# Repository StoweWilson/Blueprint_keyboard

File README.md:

## What my project is 
My project is a 64% keyboard designed to resemble the layout of an Apple Magic Keyboard, with a few keys rearranged on either side of the PCB. There will be two magnetic pogo pins on either side, which will allow the keypad with identical pogo pins to connect, as well as allowing the keypad to be placed on either side of the keyboard, therefore making it modular. The case takes inspiration from the Worklouder XYZ Work Board.

## Why I made the project
I really like low-profile 60%–65% keyboards but had trouble finding ones that fit my needs. Learning that I had to put my own spin on the idea, I decided to take on the challenge of adding a keypad while keeping it modular, so I could still have the compactness of a 64% keyboard with the ability to have a numpad that does not make it bulky.

## Images

### Keyboard

### Keypad

### Render

## BOM
### Keyboard

|Product name|Product Description|Qty|Price|Product Link|
|------------|-------------------|---|-----|------------|
|ATmega32U4-A|AVR AVR® ATmega Microcontroller IC 8-Bit 16MHz 32KB (16K x 16) FLASH 44-TQFP (10x10)|1|5.29|https://www.digikey.com/en/products/detail/microchip-technology/ATMEGA32U4-AU/1914602|
|16 MHz Crystal|CRYSTAL 3225 16MHZ 20PF 10PPM|1|.18|https://www.digikey.com/en/products/detail/eaton-electronics-division/E3X160201Y08/25656418?gclsrc=aw.ds&gad_source=1&gad_campaignid=20509818236&gbraid=0AAAAADrbLlgS94xmC2OHtv7KUQTO5uOa0&gclid=Cj0KCQiAx8PKBhD1ARIsAKsmGbeNFFstWFqMior3PH_CgvAHFOVgZvViWWTwkzizrjl1ohLOkbDwLqwaAlaHEALw_wcB|
|USB6B1 ESD Protector|TVS DIODE 5.25VWM 8SOIC|1|.69|https://www.digikey.com/en/products/detail/stmicroelectronics/USB6B1RL/654663|https://www.digikey.com/en/products/detail/amphenol-icc-fci-/10171746-00021LF/24366718?gclsrc=aw.ds&gad_source=1&gad_campaignid=20504594076&gbraid=0AAAAADrbLliKa-isyfEEG1K0mhQ-IdK9f&gclid=Cj0KCQiAx8PKBhD1ARIsAKsmGbfS4QL507NDol1-6Cdh5rUTj5M5hC5s0NrW_j3S6W67Z4K-qavOG4UaAp8YEALw_wcB|
|USB-C Receptacle (USB 2.0)|USB C RECEPTACLE R/A SMT 16P G/F|1|.72|https://www.digikey.com/en/products/detail/amphenol-icc-fci-/10171746-00021LF/24366718?gclsrc=aw.ds&gad_source=1&gad_campaignid=20504594076&gbraid=0AAAAADrbLliKa-isyfEEG1K0mhQ-IdK9f&gclid=Cj0KCQiAx8PKBhD1ARIsAKsmGbfS4QL507NDol1-6Cdh5rUTj5M5hC5s0NrW_j3S6W67Z4K-qavOG4UaAp8YEALw_wcB|
|10 kΩ|RES 10 OHM 1% 1/8W 0805|2|.11|https://www.digikey.com/en/products/detail/yageo/RC0805FR-1310RL/13694343?gclsrc=aw.ds&gad_source=1&gad_campaignid=17335707486&gbraid=0AAAAADrbLlj7rEgZ30rWPo_IyYLBKIC1T&gclid=Cj0KCQiAx8PKBhD1ARIsAKsmGbe2BlRAZ_fbKZ1YBvA79CHduwhXdcr3Sd3RQTWvr3wtoWWFxpEhsnEaAhrXEALw_wcB|
|22 Ω|RES 22 OHM 1% 1/8W 0805|2|.11|https://www.digikey.com/en/products/detail/yageo/RC0805FR-1322RL/13694339?gclsrc=aw.ds&gad_source=1&gad_campaignid=17335707486&gbraid=0AAAAADrbLlj7rEgZ30rWPo_IyYLBKIC1T&gclid=Cj0KCQiAx8PKBhD1ARIsAKsmGbfZP3-md_kWXjVo2urg73f88iKE2tR9Xip3xlEVRXTp1bbZVnmvqCgaAlWkEALw_wcB|
|5.1 kΩ|RES 5.1K OHM 5% 1/8W 0805|2|.10|https://www.digikey.com/en/products/detail/yageo/RC0805JR-075K1L/728338|
|22 pF|22 pF ±5% 50V Ceramic Capacitor C0G, NP0 0603 (1608 Metric)|2|.12|https://www.digikey.com/en/products/detail/kemet/C0603C220J5GACTU/411055|
|1 µF|CAP CER 1UF 6.3V X5R 0402|1|.08|https://www.digikey.com/en/products/detail/samsung-electro-mechanics/CL05A104KA5NNNC/3886701|
|.1uF|0.1 µF ±10% 25V Ceramic Capacitor X5R 0402 (1005 Metric)|4|.08|https://www.digikey.com/en/products/detail/samsung-electro-mechanics/CL05A104KA5NNNC/3886701|
|Diode|DIODE STANDARD 100V 150MA SOD123|64|.11|https://www.digikey.com/en/products/detail/diodes-incorporated/1N4148W-7-F/814371|
|Reset Button|SWITCH TACTILE SPST-NO 0.05A 12V|1|.41|https://www.digikey.ca/en/products/detail/c-k/Y97KT23B2NAFP/9649861|
|Adafruit 5413 Magnetic Connector|four 0.1" spaced contact pogo pins and a right angl|4|2.13|https://www.aliexpress.us/p/shoppingcart/index.html?spm=a2g0o.detail.0.0.2397nvtbnvtbTw|

### Keypad
|Product name|Product Description|Qty|Price|Product Link|
|------------|-------------------|---|-----|------------|
|XIAO RP2040 SMD|XIAO RP2040 SMD|1|4.68|https://www.digikey.com/en/products/detail/seeed-technology-co-ltd/102010428/14672129?gclsrc=aw.ds&gad_source=1&gad_campaignid=20243136172&gbraid=0AAAAADrbLlj-cx_AB7IYmSUrHfcZ3IQLC&gclid=Cj0KCQiAx8PKBhD1ARIsAKsmGbcn_ZEg4zv6ObEisLv_b6IgijRfvJiZc21Bz6JM8BaIT7ggCM4oFr8aAoSUEALw_wcB|
|PCF8575DBR I/O Expander|IC XPNDR 400KHZ I2C SMBUS 24SSOP|1|3.58|https://www.digikey.com/en/products/detail/texas-instruments/PCF8575DBR/754551|
|10 kΩ|RES 10 OHM 1% 1/8W 0805|4|.11|https://www.digikey.com/en/products/detail/yageo/RC0805FR-1310RL/13694343?gclsrc=aw.ds&gad_source=1&gad_campaignid=17335707486&gbraid=0AAAAADrbLlj7rEgZ30rWPo_IyYLBKIC1T&gclid=Cj0KCQiAx8PKBhD1ARIsAKsmGbe2BlRAZ_fbKZ1YBvA79CHduwhXdcr3Sd3RQTWvr3wtoWWFxpEhsnEaAhrXEALw_wcB|
|5.1 kΩ|RES 5.1K OHM 5% 1/8W 0805|2|.10|https://www.digikey.com/en/products/detail/yageo/RC0805JR-075K1L/728338|
|Diode|DIODE STANDARD 100V 150MA SOD123|21|.11|https://www.digikey.com/en/products/detail/diodes-incorporated/1N4148W-7-F/814371|
|Adafruit 5413 Magnetic Connector|four 0.1" spaced contact pogo pins and a right angl|4|2.13|https://www.aliexpress.us/p/shoppingcart/index.html?spm=a2g0o.detail.0.0.2397nvtbnvtbTw|

### Notes
- Shipping is not included in any of the prices.
- PCB with shippiing is $59.04 Qty of 5 each can't change.
- I will pay for the keyboard switches with my own money.

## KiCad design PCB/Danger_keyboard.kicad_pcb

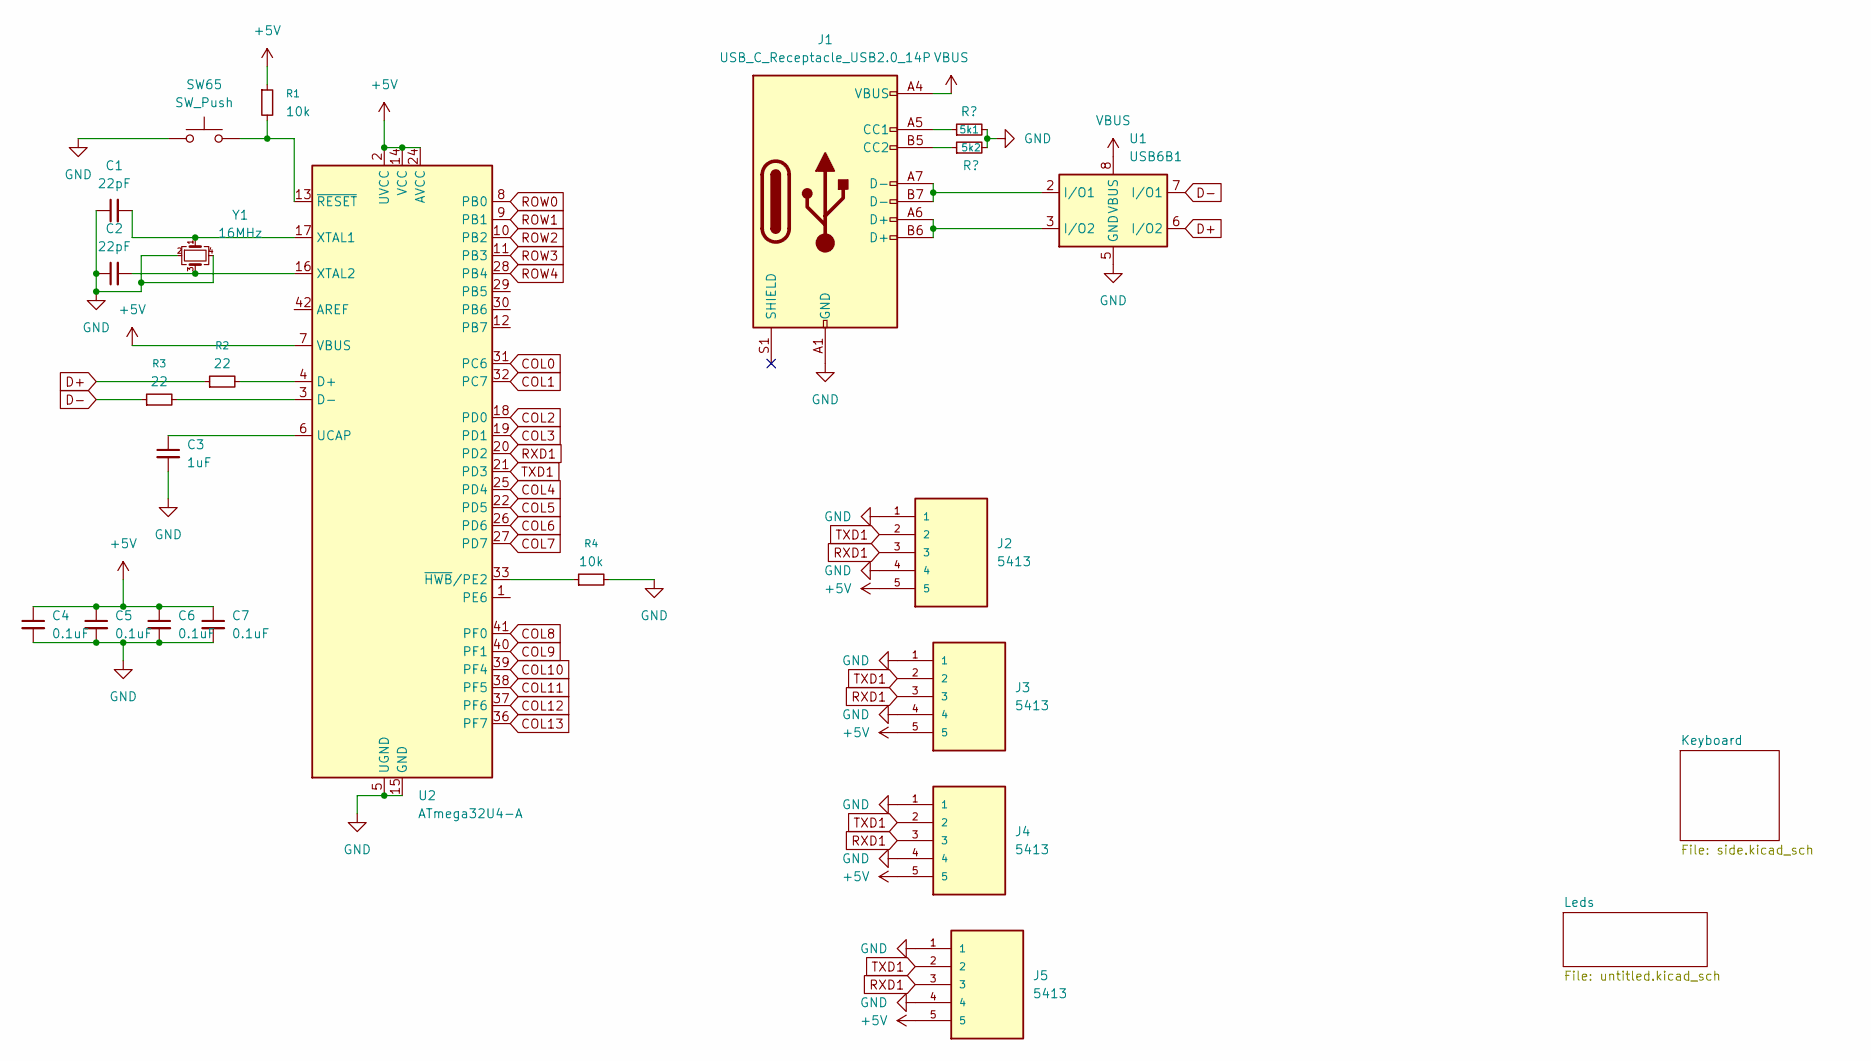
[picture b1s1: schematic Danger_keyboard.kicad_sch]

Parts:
5k1, 5k2: R?; R_0805_2012Metric
C1, C2: 22pF; C_0805_2012Metric
C3: 1uF; C_0805_2012Metric
C4, C5, C6, C7: 0.1uF; C_0805_2012Metric
J1: USB_C_Receptacle_USB2.0_14P; USB_C_Receptacle_GCT_USB4105-xx-A_16P_TopMnt_Horizontal
J2, J3, J4, J5: 5413; ADAFRUIT_5413; PARTREV X1
R1, R4: 10k; R_0805_2012Metric
R2, R3: 22; R_0805_2012Metric
SW65: SW_Push; SW_SPST_PTS647_Sx38
U1: USB6B1; SOIC-8_3.9x4.9mm_P1.27mm
U2: ATmega32U4-A; TQFP-44_10x10mm_P0.8mm
Y1: 16MHz; Crystal_SMD_3225-4Pin_3.2x2.5mm

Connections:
+5V: C4.1, C5.1, C6.1, C7.1, J2.5, J3.5, J4.5, J5.5, R1.1, U2.2 (UVCC), U2.7 (VBUS), U2.14 (VCC), U2.24 (AVCC), U2.34 (VCC), U2.44 (AVCC)
COL0: U2.31 (PC6); also elsewhere on the board
COL1: U2.32 (PC7); also elsewhere on the board
COL2: U2.18 (PD0); also elsewhere on the board
COL3: U2.19 (PD1); also elsewhere on the board
COL4: U2.25 (PD4); also elsewhere on the board
COL5: U2.22 (PD5); also elsewhere on the board
COL6: U2.26 (PD6); also elsewhere on the board
COL7: U2.27 (PD7); also elsewhere on the board
COL8: U2.41 (PF0); also elsewhere on the board
COL9: U2.40 (PF1); also elsewhere on the board
COL10: U2.39 (PF4); also elsewhere on the board
COL11: U2.38 (PF5); also elsewhere on the board
COL12: U2.37 (PF6); also elsewhere on the board
COL13: U2.36 (PF7); also elsewhere on the board
D+: R2.1, U1.6 (I/O2)
D-: R3.1, U1.7 (I/O1)
GND: 5k1.2, 5k2.2, C1.1, C2.1, C3.2, C4.2, C5.2, C6.2, C7.2, J1.A1 (GND), J1.A12 (GND), J1.B1 (GND), J1.B12 (GND), J2.1, J2.4, J3.1, J3.4, J4.1, J4.4, J5.1, J5.4, R4.2, SW65.1, U1.4 (GND), U1.5 (GND), U2.5 (UGND), U2.15 (GND), U2.23 (GND), U2.35 (GND), U2.43 (GND), Y1.2, Y1.4
unnamed: 5k1.1, J1.A5 (CC1)
unnamed: 5k2.1, J1.B5 (CC2)
unnamed: J1.A6 (D+), J1.B6 (D+), U1.3 (I/O2)
unnamed: J1.A7 (D-), J1.B7 (D-), U1.2 (I/O1)
unnamed: R2.2, U2.4 (D+)
unnamed: R3.2, U2.3 (D-)
unnamed: C3.1, U2.6 (UCAP)
unnamed: C1.2, U2.17 (XTAL1), Y1.1
unnamed: C2.2, U2.16 (XTAL2), Y1.3
unnamed: R4.1, U2.33 (~HWB/PE2)
unnamed: R1.2, SW65.2, U2.13 (~RESET)
ROW0: U2.8 (PB0); also elsewhere on the board
ROW1: U2.9 (PB1); also elsewhere on the board
ROW2: U2.10 (PB2); also elsewhere on the board
ROW3: U2.11 (PB3); also elsewhere on the board
ROW4: U2.28 (PB4); also elsewhere on the board
RXD1: J2.3, J3.3, J4.3, J5.3, U2.20 (PD2)
TXD1: J2.2, J3.2, J4.2, J5.2, U2.21 (PD3)
VBUS: J1.A4 (VBUS), J1.A9 (VBUS), J1.B4 (VBUS), J1.B9 (VBUS), U1.1 (VBUS), U1.8 (VBUS)

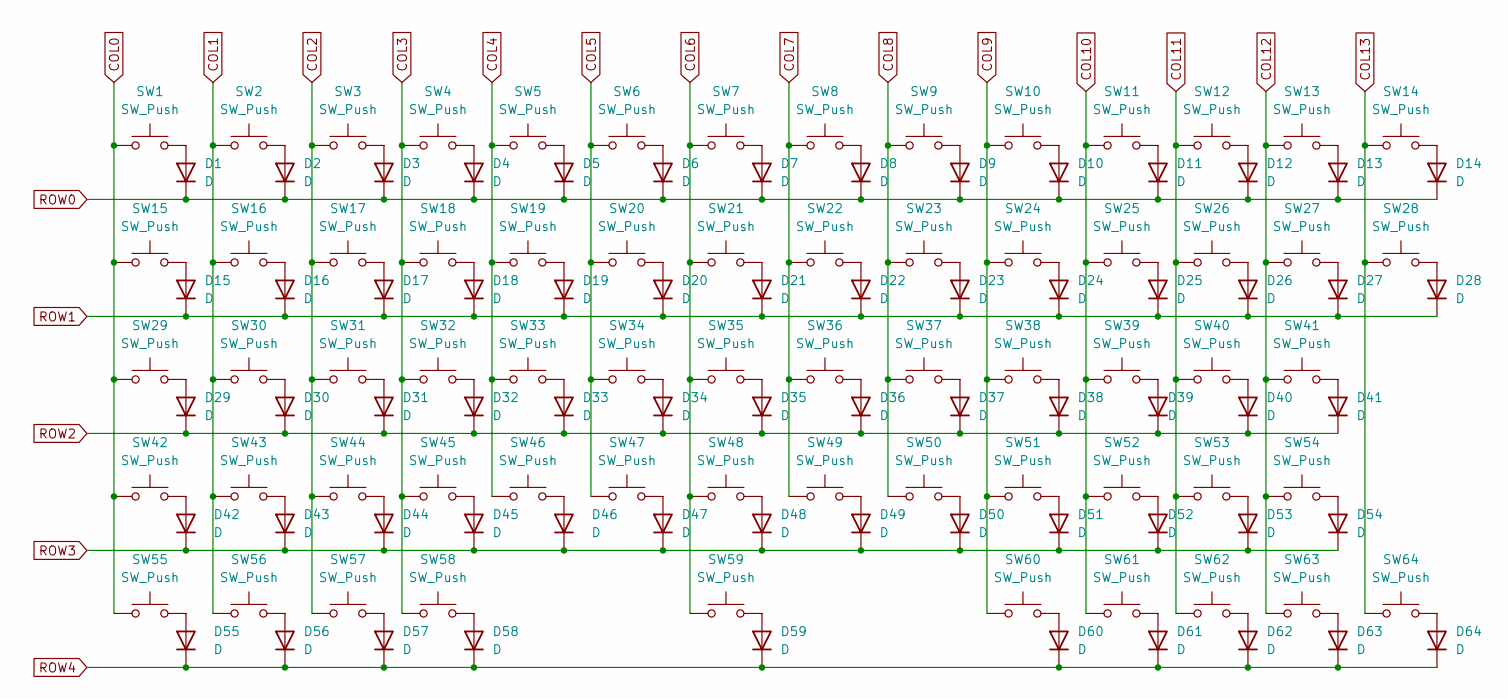
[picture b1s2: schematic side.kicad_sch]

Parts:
D1, D2, D3, D4, D5, D6, D7, D8, D9, D10, D11, D12, D13, D14, D15, D16, D17, D18, D19, D20, D21, D22, D23, D24, D25, D26, D27, D28, D29, D30, D31, D32, D33, D34, D35, D36, D37, D38, D39, D40, D41, D42, D43, D44, D45, D46, D47, D48, D49, D50, D51, D52, D53, D54, D55, D56, D57, D58, D59, D60, D61, D62, D63, D64: D; D_SOD-123
SW1, SW2, SW3, SW4, SW5, SW6, SW7, SW8, SW9, SW10, SW11, SW12, SW13, SW14, SW15, SW16, SW17, SW18, SW19, SW20, SW21, SW22, SW23, SW24, SW25, SW26, SW27, SW28, SW29, SW30, SW31, SW32, SW33, SW34, SW35, SW36, SW37, SW38, SW39, SW40, SW41, SW42, SW43, SW44, SW45, SW46, SW47, SW48, SW49, SW50, SW51, SW52, SW53, SW54, SW55, SW56, SW57, SW58, SW59, SW60, SW61, SW62, SW63, SW64: SW_Push; SW_Gateron_LowProfile_HotSwap_PTH

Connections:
COL0: SW1.1, SW15.1, SW29.1, SW42.1, SW55.1; also elsewhere on the board
COL1: SW2.1, SW16.1, SW30.1, SW43.1, SW56.1; also elsewhere on the board
COL2: SW3.1, SW17.1, SW31.1, SW44.1, SW57.1; also elsewhere on the board
COL3: SW4.1, SW18.1, SW32.1, SW45.1, SW58.1; also elsewhere on the board
COL4: SW5.1, SW19.1, SW33.1, SW46.1; also elsewhere on the board
COL5: SW6.1, SW20.1, SW34.1, SW47.1; also elsewhere on the board
COL6: SW7.1, SW21.1, SW35.1, SW48.1, SW59.1; also elsewhere on the board
COL7: SW8.1, SW22.1, SW36.1, SW49.1; also elsewhere on the board
COL8: SW9.1, SW23.1, SW37.1, SW50.1; also elsewhere on the board
COL9: SW10.1, SW24.1, SW38.1, SW51.1, SW60.1; also elsewhere on the board
COL10: SW11.1, SW25.1, SW39.1, SW52.1, SW61.1; also elsewhere on the board
COL11: SW12.1, SW26.1, SW40.1, SW53.1, SW62.1; also elsewhere on the board
COL12: SW13.1, SW27.1, SW41.1, SW54.1, SW63.1; also elsewhere on the board
COL13: SW14.1, SW28.1, SW64.1; also elsewhere on the board
unnamed: D1.2 (A), SW1.2
unnamed: D2.2 (A), SW2.2
unnamed: D3.2 (A), SW3.2
unnamed: D4.2 (A), SW4.2
unnamed: D5.2 (A), SW5.2
unnamed: D6.2 (A), SW6.2
unnamed: D7.2 (A), SW7.2
unnamed: D8.2 (A), SW8.2
unnamed: D9.2 (A), SW9.2
unnamed: D10.2 (A), SW10.2
unnamed: D11.2 (A), SW11.2
unnamed: D12.2 (A), SW12.2
unnamed: D13.2 (A), SW13.2
unnamed: D14.2 (A), SW14.2
unnamed: D15.2 (A), SW15.2
unnamed: D16.2 (A), SW16.2
unnamed: D17.2 (A), SW17.2
unnamed: D18.2 (A), SW18.2
unnamed: D19.2 (A), SW19.2
unnamed: D20.2 (A), SW20.2
unnamed: D21.2 (A), SW21.2
unnamed: D22.2 (A), SW22.2
unnamed: D23.2 (A), SW23.2
unnamed: D24.2 (A), SW24.2
unnamed: D25.2 (A), SW25.2
unnamed: D26.2 (A), SW26.2
unnamed: D27.2 (A), SW27.2
unnamed: D28.2 (A), SW28.2
unnamed: D29.2 (A), SW29.2
unnamed: D30.2 (A), SW30.2
unnamed: D31.2 (A), SW31.2
unnamed: D32.2 (A), SW32.2
unnamed: D33.2 (A), SW33.2
unnamed: D34.2 (A), SW34.2
unnamed: D35.2 (A), SW35.2
unnamed: D36.2 (A), SW36.2
unnamed: D37.2 (A), SW37.2
unnamed: D38.2 (A), SW38.2
unnamed: D39.2 (A), SW39.2
unnamed: D40.2 (A), SW40.2
unnamed: D41.2 (A), SW41.2
unnamed: D42.2 (A), SW42.2
unnamed: D43.2 (A), SW43.2
unnamed: D44.2 (A), SW44.2
unnamed: D45.2 (A), SW45.2
unnamed: D46.2 (A), SW46.2
unnamed: D47.2 (A), SW47.2
unnamed: D48.2 (A), SW48.2
unnamed: D49.2 (A), SW49.2
unnamed: D50.2 (A), SW50.2
unnamed: D51.2 (A), SW51.2
unnamed: D52.2 (A), SW52.2
unnamed: D53.2 (A), SW53.2
unnamed: D54.2 (A), SW54.2
unnamed: D55.2 (A), SW55.2
unnamed: D56.2 (A), SW56.2
unnamed: D57.2 (A), SW57.2
unnamed: D58.2 (A), SW58.2
unnamed: D59.2 (A), SW59.2
unnamed: D60.2 (A), SW60.2
unnamed: D61.2 (A), SW61.2
unnamed: D62.2 (A), SW62.2
unnamed: D63.2 (A), SW63.2
unnamed: D64.2 (A), SW64.2
ROW0: D1.1 (K), D2.1 (K), D3.1 (K), D4.1 (K), D5.1 (K), D6.1 (K), D7.1 (K), D8.1 (K), D9.1 (K), D10.1 (K), D11.1 (K), D12.1 (K), D13.1 (K), D14.1 (K); also elsewhere on the board
ROW1: D15.1 (K), D16.1 (K), D17.1 (K), D18.1 (K), D19.1 (K), D20.1 (K), D21.1 (K), D22.1 (K), D23.1 (K), D24.1 (K), D25.1 (K), D26.1 (K), D27.1 (K), D28.1 (K); also elsewhere on the board
ROW2: D29.1 (K), D30.1 (K), D31.1 (K), D32.1 (K), D33.1 (K), D34.1 (K), D35.1 (K), D36.1 (K), D37.1 (K), D38.1 (K), D39.1 (K), D40.1 (K), D41.1 (K); also elsewhere on the board
ROW3: D42.1 (K), D43.1 (K), D44.1 (K), D45.1 (K), D46.1 (K), D47.1 (K), D48.1 (K), D49.1 (K), D50.1 (K), D51.1 (K), D52.1 (K), D53.1 (K), D54.1 (K); also elsewhere on the board
ROW4: D55.1 (K), D56.1 (K), D57.1 (K), D58.1 (K), D59.1 (K), D60.1 (K), D61.1 (K), D62.1 (K), D63.1 (K), D64.1 (K); also elsewhere on the board

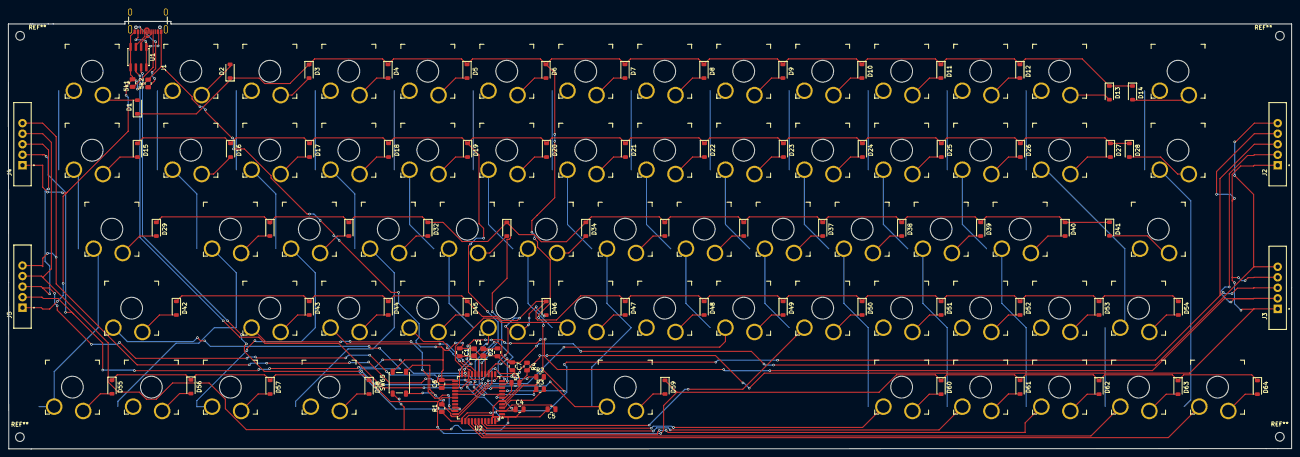
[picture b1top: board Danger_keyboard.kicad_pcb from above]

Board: 2 copper layers, 309.5 x 103.1 mm, 150 parts (0 on the bottom side), 101 nets.

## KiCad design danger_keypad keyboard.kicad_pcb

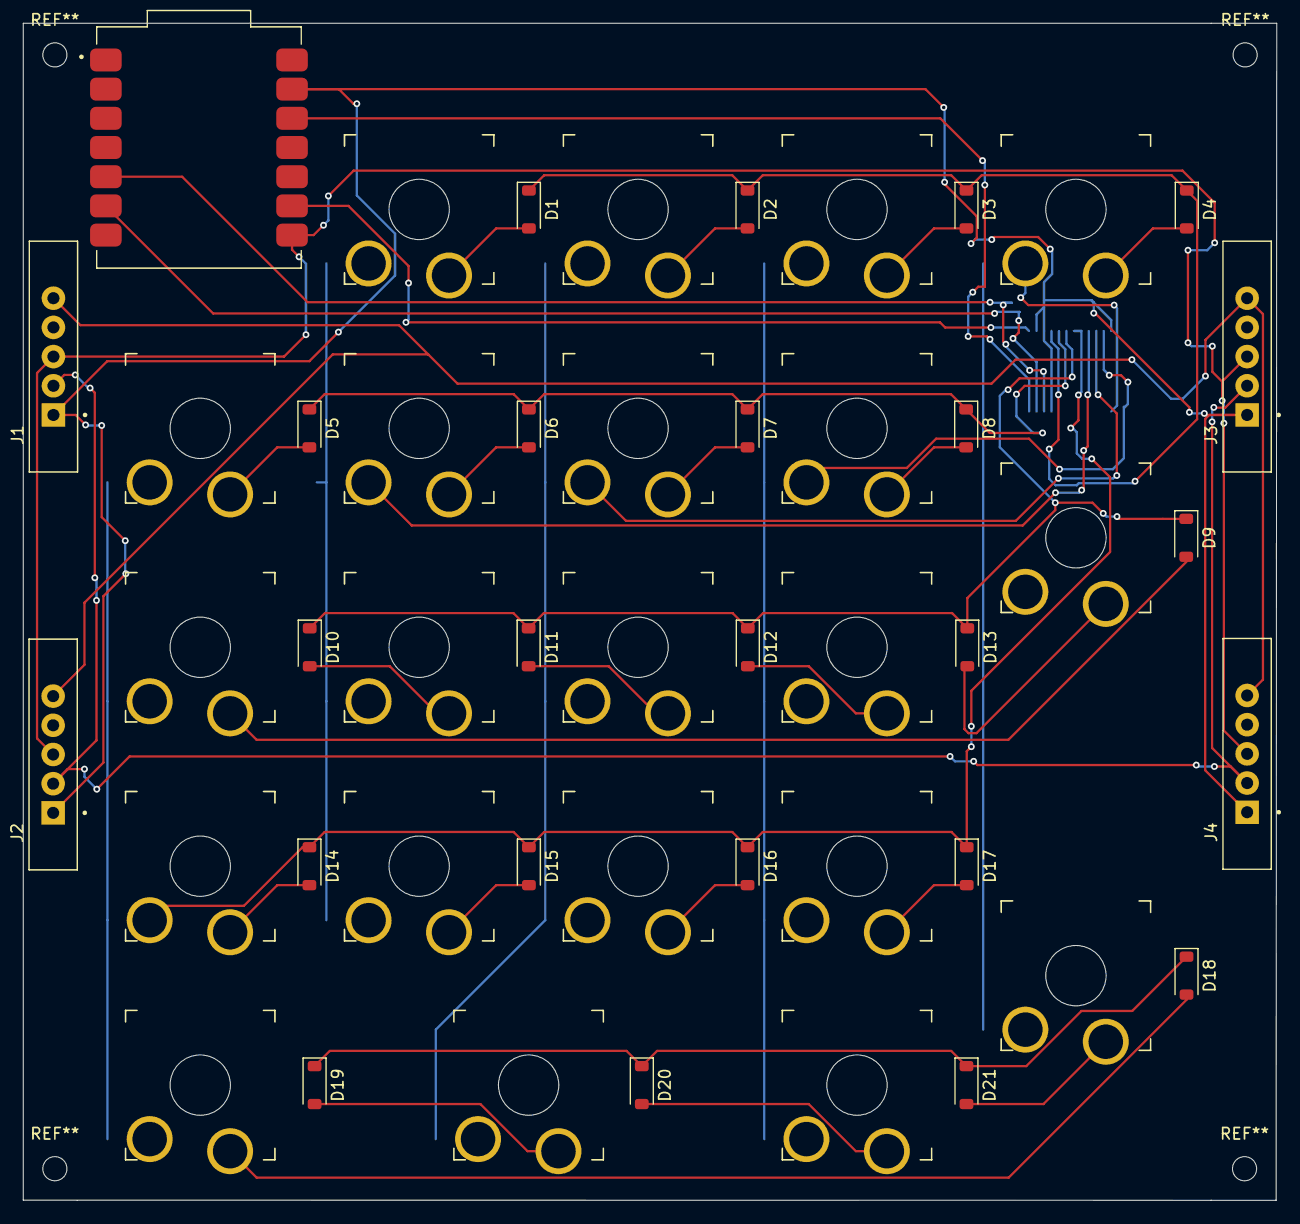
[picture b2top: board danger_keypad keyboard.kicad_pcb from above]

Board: 2 copper layers, 109.1 x 102.4 mm, 48 parts (1 on the bottom side), 38 nets.

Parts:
D1, D2, D3, D4, D5, D6, D7, D8, D9, D10, D11, D12, D13, D14, D15, D16, D17, D18, D19, D20, D21: D; D_SOD-123
J1, J2, J3, J4: 5413; ADAFRUIT_5413
SW1, SW2, SW3, SW4, SW5, SW6, SW7, SW8, SW9, SW10, SW11, SW12, SW13, SW14, SW15, SW16, SW17, SW18, SW19, SW20, SW21: SW_Push; SW_Gateron_LowProfile_HotSwap_PTH
U1: XIAO-RP2040-SMD; MODULE_102010428
U2: PCF8575DBR; SSOP-24_5.3x8.2mm_P0.65mm

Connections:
3V: U1.12 (3V3), U2.24 (VCC)
+5V: J1.5, J2.5, J3.5, J4.5
GND: J1.1, J2.1, J3.1, J4.1, U1.13 (GND), U2.2 (A1), U2.3 (A2), U2.12 (GND), U2.21 (A0)
Key_Col1: D14.1 (K), D15.1 (K), D16.1 (K), D17.1 (K), SW5.1, SW10.1, SW14.1, SW19.1, U2.7 (P3), U2.8 (P4)
Key_Col2: SW1.1, SW6.1, SW11.1, SW15.1, U2.9 (P5)
Key_Col3: SW2.1, SW7.1, SW12.1, SW16.1, SW20.1, U2.10 (P6)
Key_Col4: SW3.1, SW8.1, SW13.1, SW17.1, SW21.1, U2.11 (P7)
Key_Col5: SW4.1, SW9.1, SW18.1, U2.13 (P10)
Key_Row1: D1.1 (K), D2.1 (K), D3.1 (K), D4.1 (K), U2.4 (P0)
Key_Row2: D5.1 (K), D6.1 (K), D7.1 (K), D8.1 (K), U2.5 (P1)
Key_Row3: D9.1 (K), D10.1 (K), D11.1 (K), D12.1 (K), D13.1 (K), U2.6 (P2)
Key_Row5: D18.1 (K), D19.1 (K), D20.1 (K), D21.1 (K)
MCP_INT: U1.9 (GPIO2_D8_SCK), U2.1 (~INT)
unnamed: D1.2 (A), SW1.2
unnamed: D2.2 (A), SW2.2
unnamed: D3.2 (A), SW3.2
unnamed: D4.2 (A), SW4.2
unnamed: D5.2 (A), SW5.2
unnamed: D6.2 (A), SW6.2
unnamed: D7.2 (A), SW7.2
unnamed: D8.2 (A), SW8.2
unnamed: D9.2 (A), SW10.2
unnamed: D10.2 (A), SW11.2
unnamed: D11.2 (A), SW12.2
unnamed: D12.2 (A), SW13.2
unnamed: D13.2 (A), SW9.2
unnamed: D14.2 (A), SW14.2
unnamed: D15.2 (A), SW15.2
unnamed: D16.2 (A), SW16.2
unnamed: D17.2 (A), SW17.2
unnamed: D18.2 (A), SW19.2
unnamed: D19.2 (A), SW20.2
unnamed: D20.2 (A), SW21.2
unnamed: D21.2 (A), SW18.2
RX: J1.3, J2.3, J3.3, J4.3, U1.8 (GPIO1_D7_CSn_RX)
SCL: U1.6 (GPIO7_D5_SCL), U2.23 (SDA)
SDA: U1.5 (GPIO6_D4_SDA), U2.22 (SCL)
TK: J1.2, J2.2, J3.2, J4.2

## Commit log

2025-12-07 keyboard
2025-12-14 My pcb stuff
    hopefully all of it
2025-12-14 Create PCB
2025-12-14 folder
2025-12-27 folders
2025-12-27 code
2025-12-28 Add Bill of Materials for keyboard PCBs
    Added a Bill of Materials (BOM) section with details for the Main Keyboard PCB and Keypad/Expansion PCB, including components, quantities, and links to datasheets.
2025-12-29 Add prices and links to BOM in README.md
    Updated the Bill of Materials (BOM) with prices and links for components.
2025-12-29 Update Reset Button price and link in README
    Updated the price and link for the Reset Button.
2025-12-29 Update component prices and links in README
2025-12-29 Add PCB pricing and links to README
2025-12-29 Fix table formatting in README.md
2025-12-29 Fix formatting in PCB reference table
2025-12-29 Update README with PCB details and shipping note
    Added PCB entry and shipping note to the README.
2025-12-29 Update PCB pricing details in README
    Correct the pricing information for PCB with shipping.
2025-12-30 Add project images to README
    Added project images section with relevant images.
2025-12-30 images
2025-12-30 Fix image filenames in README.md
    Updated image filenames for consistency in README.
2025-12-30 folder images
2025-12-30 Fix image filenames in README.md
    Updated image filenames in README for consistency.
2025-12-30 Remove project images from README
    Removed project images section from README.
2025-12-30 case
2025-12-30 Update README with subtotal and shipping estimates
    Added subtotal and estimated shipping costs to the README.
2025-12-30 Fix component links and update prices in README
    Updated the link for ATmega32U4-A and adjusted the price for C1, C2.
2025-12-30 Update C4–C7 price and supplier link
    Updated the price and link for capacitor C4–C7.
2026-01-02 Revise project overview and BOM details
    Updated project description and added images for keyboard and keypad. Revised BOM details and notes.
2026-01-02 move in right places
2026-01-02 messed up the BOM fixed it
2026-01-02 moved
2026-01-02 Add 0.1 µF capacitor to component list in README
2026-01-02 new files making sure everything is up to date
2026-01-02 Revise README for clarity and grammar improvements
    Corrected grammar and improved clarity in project description and rationale.
2026-01-03 whoa my code
2026-01-03 new firm
2026-01-03 Revise prices and links in README BOM
    Updated product prices and links in BOM section.
2026-01-16 fixed
2026-01-16 Update images in README for keyboard and render
    Removed old images and added new screenshots for keyboard and render sections.
2026-01-27 Add screenshots to README for keyboard and keypad
    Added additional screenshots for keyboard, keypad, and render sections.
